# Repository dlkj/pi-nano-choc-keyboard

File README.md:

# pi-nano-choc-keyboard
Split ergo keyboard based on the Rasberry Pi Nano and Kailh Choc v1 switches

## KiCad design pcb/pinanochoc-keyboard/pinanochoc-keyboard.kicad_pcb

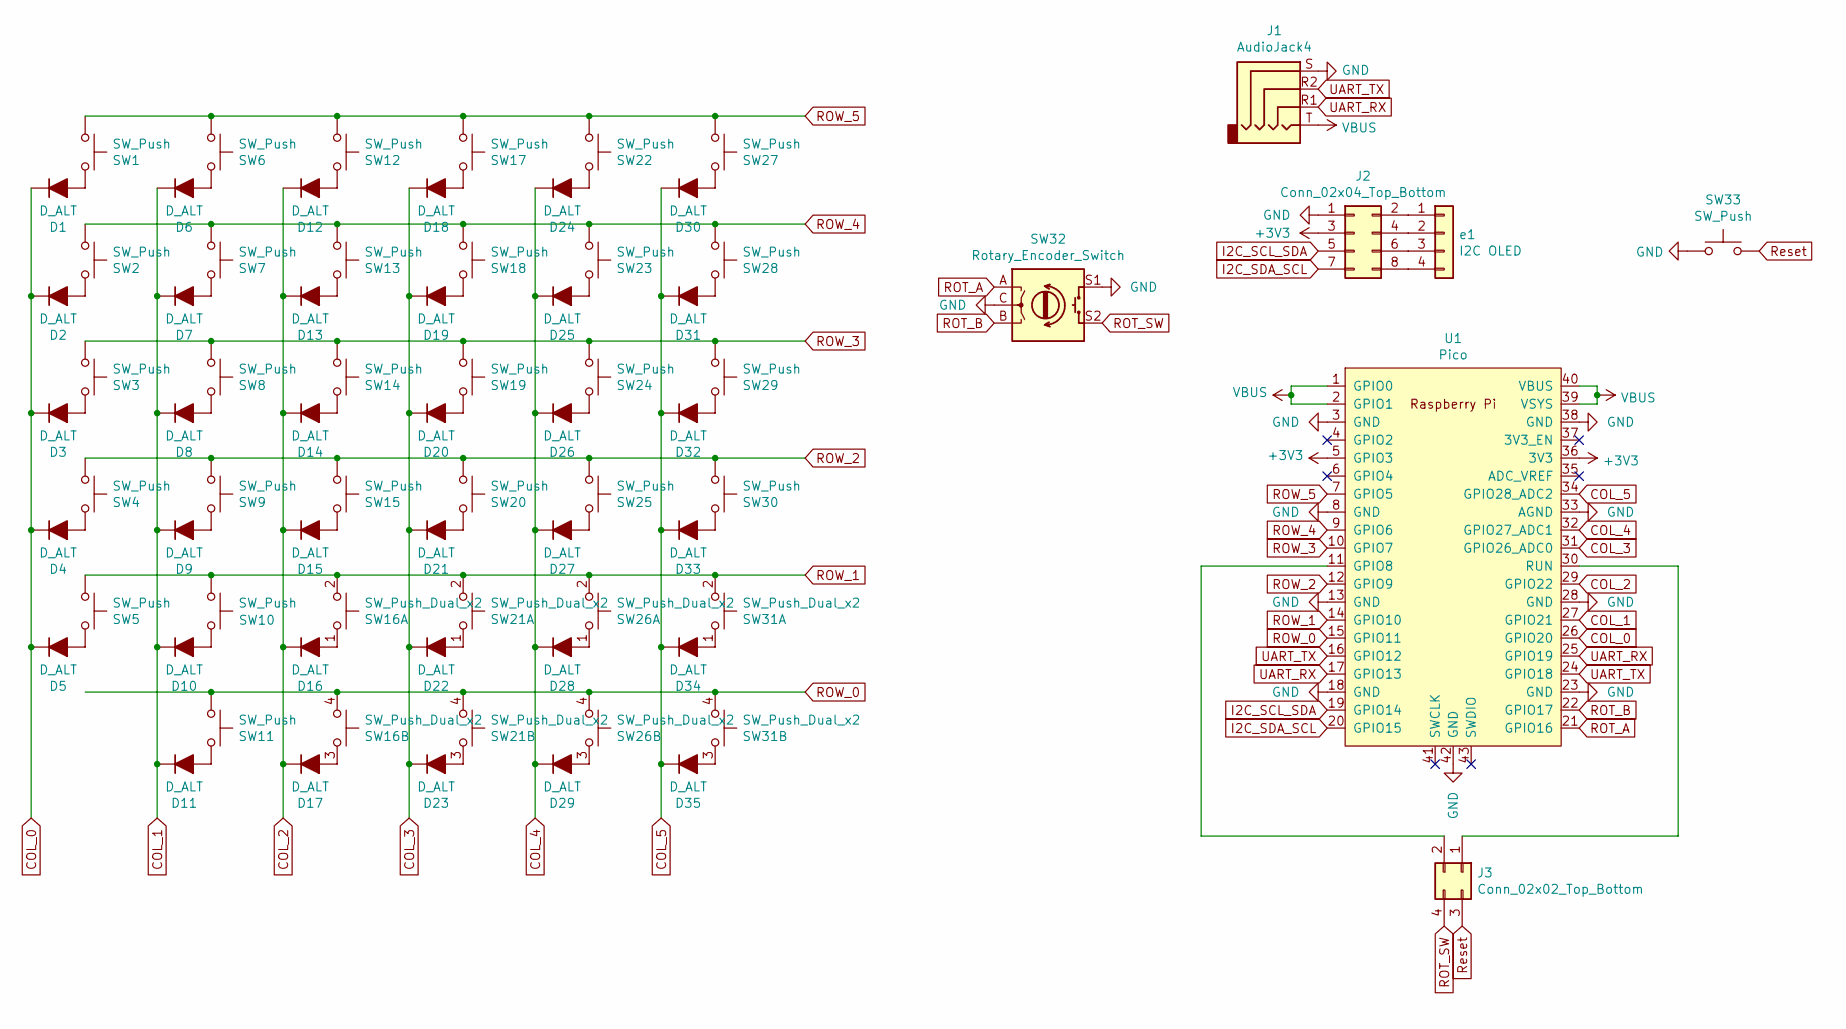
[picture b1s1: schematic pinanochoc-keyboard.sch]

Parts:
D1, D2, D3, D4, D5, D6, D7, D8, D9, D10, D11, D12, D13, D14, D15, D16, D17, D18, D19, D20, D21, D22, D23, D24, D25, D26, D27, D28, D29, D30, D31, D32, D33, D34, D35: D_ALT; D_DO-35_SOD27_P7.62mm_Horizontal
J1: AudioJack4; TRRS-PJ-320A_reversable
J2: Conn_02x04_Top_Bottom; PinHeader_2x04_P2.54mm_Vertical
J3: Conn_02x02_Top_Bottom; PinHeader_2x02_P2.54mm_Vertical
SW1, SW2, SW3, SW4, SW5, SW6, SW7, SW8, SW9, SW10, SW11, SW12, SW13, SW14, SW15, SW17, SW18, SW19, SW20, SW22, SW23, SW24, SW25, SW27, SW28, SW29, SW30: SW_Push; SW_PG1350_reversible
SW16, SW21, SW26, SW31: SW_Push_Dual_x2; SW_PG1350_reversible_double_rotatable
SW32: Rotary_Encoder_Switch; RotaryEncoder_Alps_EC11E-Switch_Vertical_H20mm
SW33: SW_Push; SW_PUSH_6mm
U1: Pico; RPi_Pico_SMD_TH_flipable
e1: I2C OLED; PinHeader_1x04_P2.54mm_Vertical

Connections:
+3V3: J2.3, U1.5 (GPIO3), U1.36 (3V3)
COL_0: D1.1 (K), D2.1 (K), D3.1 (K), D4.1 (K), D5.1 (K), U1.26 (GPIO20)
COL_1: D6.1 (K), D7.1 (K), D8.1 (K), D9.1 (K), D10.1 (K), D11.1 (K), U1.27 (GPIO21)
COL_2: D12.1 (K), D13.1 (K), D14.1 (K), D15.1 (K), D16.1 (K), D17.1 (K), U1.29 (GPIO22)
COL_3: D18.1 (K), D19.1 (K), D20.1 (K), D21.1 (K), D22.1 (K), D23.1 (K), U1.31 (GPIO26_ADC0)
COL_4: D24.1 (K), D25.1 (K), D26.1 (K), D27.1 (K), D28.1 (K), D29.1 (K), U1.32 (GPIO27_ADC1)
COL_5: D30.1 (K), D31.1 (K), D32.1 (K), D33.1 (K), D34.1 (K), D35.1 (K), U1.34 (GPIO28_ADC2)
GND: J1.S, J2.1, SW32.C, SW32.S1, SW33.1, U1.3 (GND), U1.8 (GND), U1.13 (GND), U1.18 (GND), U1.23 (GND), U1.28 (GND), U1.33 (AGND), U1.38 (GND), U1.42 (GND)
I2C_SCL_SDA: J2.5, U1.19 (GPIO14)
I2C_SDA_SCL: J2.7, U1.20 (GPIO15)
unnamed: D1.2 (A), SW1.1
unnamed: D2.2 (A), SW2.1
unnamed: D3.2 (A), SW3.1
unnamed: D4.2 (A), SW4.1
unnamed: D5.2 (A), SW5.1
unnamed: D6.2 (A), SW6.1
unnamed: D7.2 (A), SW7.1
unnamed: D8.2 (A), SW8.1
unnamed: D9.2 (A), SW9.1
unnamed: D10.2 (A), SW10.1
unnamed: D11.2 (A), SW11.1
unnamed: D12.2 (A), SW12.1
unnamed: D13.2 (A), SW13.1
unnamed: D14.2 (A), SW14.1
unnamed: D15.2 (A), SW15.1
unnamed: D16.2 (A), SW16.1 (C)
unnamed: D17.2 (A), SW16.3 (C)
unnamed: D18.2 (A), SW17.1
unnamed: D19.2 (A), SW18.1
unnamed: D20.2 (A), SW19.1
unnamed: D21.2 (A), SW20.1
unnamed: D22.2 (A), SW21.1 (C)
unnamed: D23.2 (A), SW21.3 (C)
unnamed: D24.2 (A), SW22.1
unnamed: D25.2 (A), SW23.1
unnamed: D26.2 (A), SW24.1
unnamed: D27.2 (A), SW25.1
unnamed: D28.2 (A), SW26.1 (C)
unnamed: D29.2 (A), SW26.3 (C)
unnamed: D30.2 (A), SW27.1
unnamed: D31.2 (A), SW28.1
unnamed: D32.2 (A), SW29.1
unnamed: D33.2 (A), SW30.1
unnamed: D34.2 (A), SW31.1 (C)
unnamed: D35.2 (A), SW31.3 (C)
unnamed: J2.2, e1.1
unnamed: J2.4, e1.2
unnamed: J2.6, e1.3
unnamed: J2.8, e1.4
unnamed: J3.1, U1.30 (RUN)
unnamed: J3.2, U1.11 (GPIO8)
ROT_A: SW32.A, U1.21 (GPIO16)
ROT_B: SW32.B, U1.22 (GPIO17)
ROT_SW: J3.4, SW32.S2
ROW_0: SW11.2, SW16.4 (D), SW21.4 (D), SW26.4 (D), SW31.4 (D), U1.15 (GPIO11)
ROW_1: SW5.2, SW10.2, SW16.2 (D), SW21.2 (D), SW26.2 (D), SW31.2 (D), U1.14 (GPIO10)
ROW_2: SW4.2, SW9.2, SW15.2, SW20.2, SW25.2, SW30.2, U1.12 (GPIO9)
ROW_3: SW3.2, SW8.2, SW14.2, SW19.2, SW24.2, SW29.2, U1.10 (GPIO7)
ROW_4: SW2.2, SW7.2, SW13.2, SW18.2, SW23.2, SW28.2, U1.9 (GPIO6)
ROW_5: SW1.2, SW6.2, SW12.2, SW17.2, SW22.2, SW27.2, U1.7 (GPIO5)
Reset: J3.3, SW33.2
UART_RX: J1.R1, U1.17 (GPIO13), U1.25 (GPIO19)
UART_TX: J1.R2, U1.16 (GPIO12), U1.24 (GPIO18)
VBUS: J1.T, U1.1 (GPIO0), U1.2 (GPIO1), U1.39 (VSYS), U1.40 (VBUS)

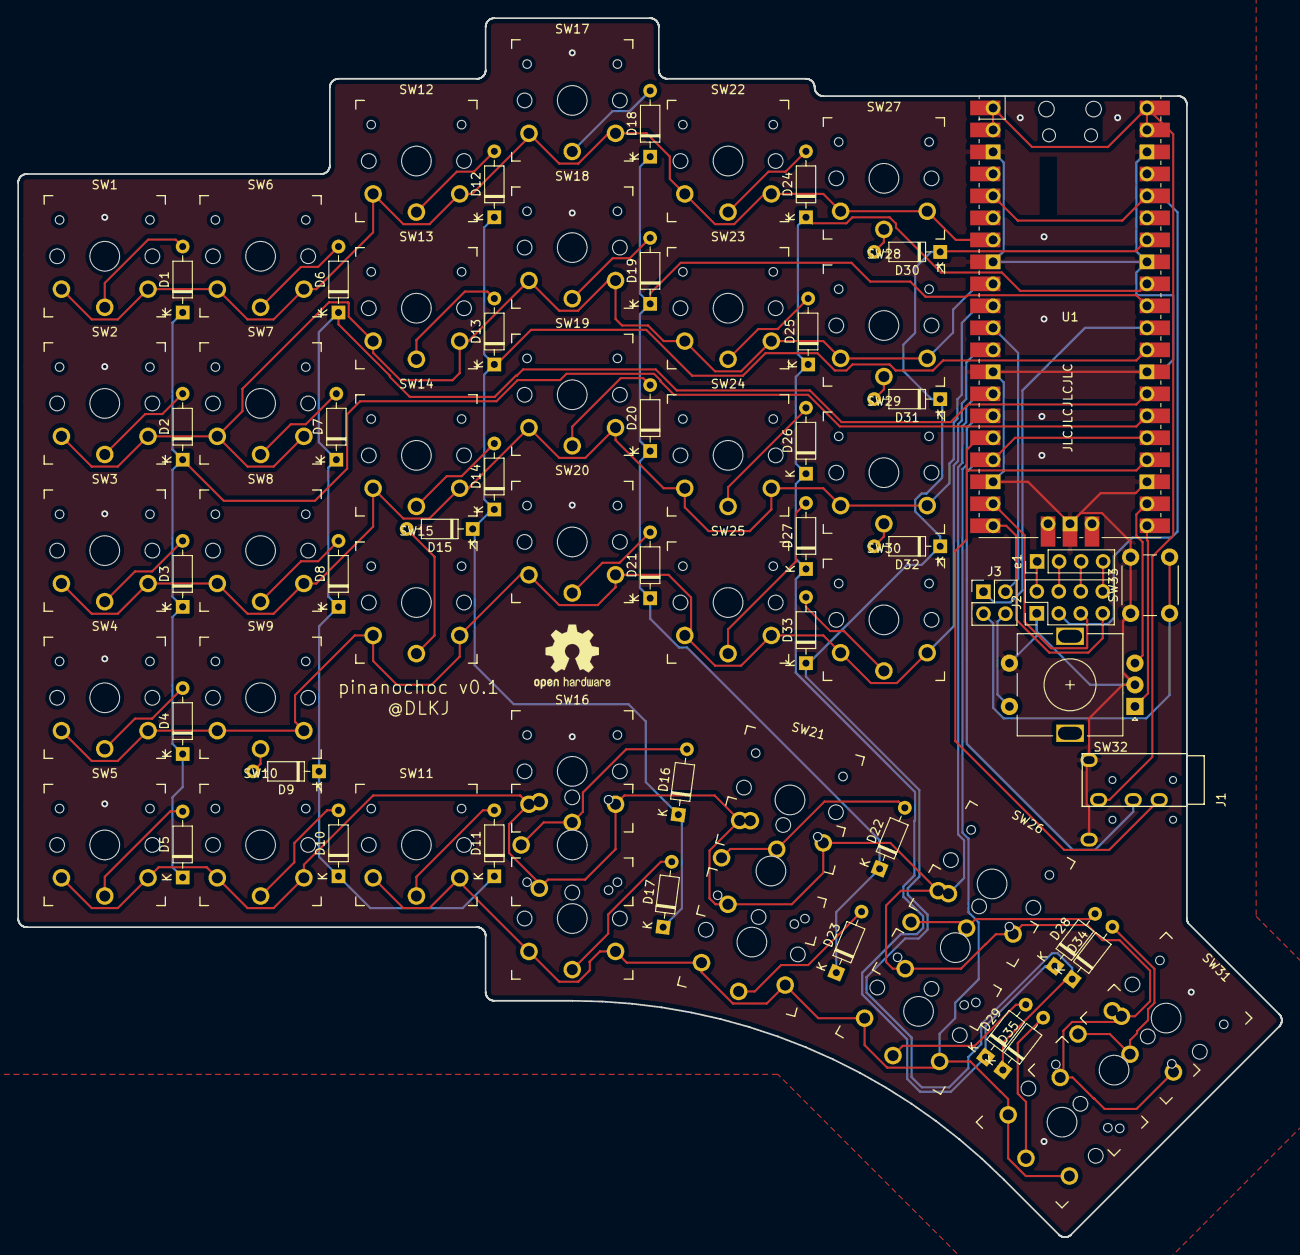
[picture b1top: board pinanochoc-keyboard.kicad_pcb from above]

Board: 2 copper layers, 146.0 x 140.8 mm, 73 parts (0 on the bottom side), 64 nets.

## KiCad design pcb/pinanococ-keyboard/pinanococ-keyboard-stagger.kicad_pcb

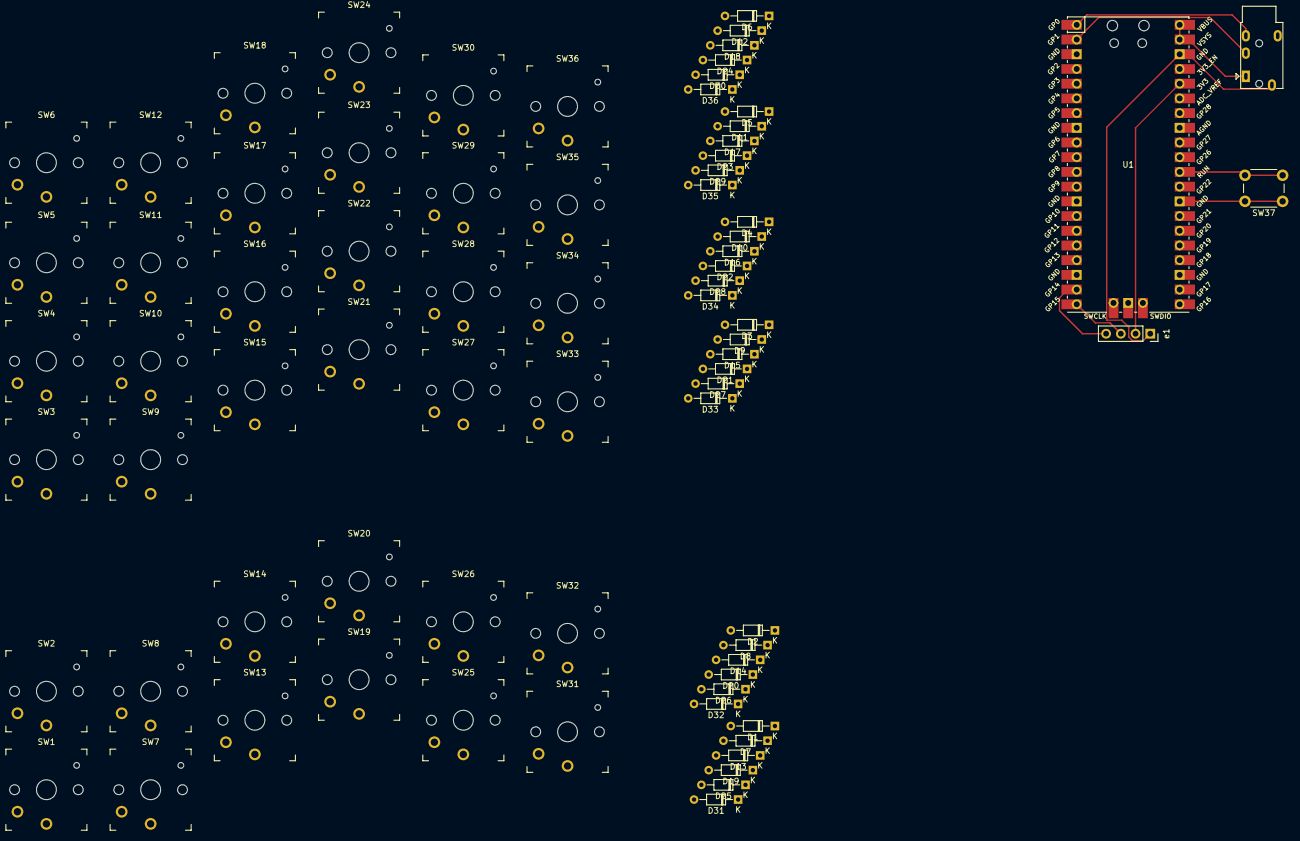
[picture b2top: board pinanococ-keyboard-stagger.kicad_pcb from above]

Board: 2 copper layers, 76 parts (0 on the bottom side), 57 nets.

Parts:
D1, D2, D3, D4, D5, D6, D7, D8, D9, D10, D11, D12, D13, D14, D15, D16, D17, D18, D19, D20, D21, D22, D23, D24, D25, D26, D27, D28, D29, D30, D31, D32, D33, D34, D35, D36: D_ALT; D_DO-34_SOD68_P7.62mm_Horizontal
J1: AudioJack4; Jack_3.5mm_PJ320E_Horizontal
SW1, SW2, SW3, SW4, SW5, SW6, SW7, SW8, SW9, SW10, SW11, SW12, SW13, SW14, SW15, SW16, SW17, SW18, SW19, SW20, SW21, SW22, SW23, SW24, SW25, SW26, SW27, SW28, SW29, SW30, SW31, SW32, SW33, SW34, SW35, SW36: SW_Push; SW_PG1350
SW37: SW_Push; SW_PUSH_6mm
U1: Pico; RPi_Pico_SMD_TH
e1: I2C OLED; PinSocket_1x04_P2.54mm_Vertical

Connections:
+3V3: U1.36, e1.2
COL_0: D1.1, D2.1, D3.1, D4.1, D5.1, D6.1, U1.11
COL_1: D7.1, D8.1, D9.1, D10.1, D11.1, D12.1, U1.12
COL_2: D13.1, D14.1, D15.1, D16.1, D17.1, D18.1, U1.14
COL_3: D19.1, D20.1, D21.1, D22.1, D23.1, D24.1, U1.15
COL_4: D25.1, D26.1, D27.1, D28.1, D29.1, D30.1, U1.16
COL_5: D31.1, D32.1, D33.1, D34.1, D35.1, D36.1, U1.17
GND: J1.S, U1.38, e1.1
GND1: SW37.1, U1.28
I2C_SCL: U1.20, e1.3
I2C_SDA: U1.19, e1.4
unnamed: D1.2, SW1.1
unnamed: D2.2, SW2.1
unnamed: D3.2, SW3.1
unnamed: D4.2, SW4.1
unnamed: D5.2, SW5.1
unnamed: D6.2, SW6.1
unnamed: D7.2, SW7.1
unnamed: D8.2, SW8.1
unnamed: D9.2, SW9.1
unnamed: D10.2, SW10.1
unnamed: D11.2, SW11.1
unnamed: D12.2, SW12.1
unnamed: D13.2, SW13.1
unnamed: D14.2, SW14.1
unnamed: D15.2, SW15.1
unnamed: D16.2, SW16.1
unnamed: D17.2, SW17.1
unnamed: D18.2, SW18.1
unnamed: D19.2, SW19.1
unnamed: D20.2, SW20.1
unnamed: D21.2, SW21.1
unnamed: D22.2, SW22.1
unnamed: D23.2, SW23.1
unnamed: D24.2, SW24.1
unnamed: D25.2, SW25.1
unnamed: D26.2, SW26.1
unnamed: D27.2, SW27.1
unnamed: D28.2, SW28.1
unnamed: D29.2, SW29.1
unnamed: D30.2, SW30.1
unnamed: D31.2, SW31.1
unnamed: D32.2, SW32.1
unnamed: D33.2, SW33.1
unnamed: D34.2, SW34.1
unnamed: D35.2, SW35.1
unnamed: D36.2, SW36.1
ROW_0: SW1.2, SW7.2, SW13.2, SW19.2, SW25.2, SW31.2, U1.4
ROW_1: SW2.2, SW8.2, SW14.2, SW20.2, SW26.2, SW32.2, U1.5
ROW_2: SW3.2, SW9.2, SW15.2, SW21.2, SW27.2, SW33.2, U1.6
ROW_3: SW4.2, SW10.2, SW16.2, SW22.2, SW28.2, SW34.2, U1.7
ROW_4: SW5.2, SW11.2, SW17.2, SW23.2, SW29.2, SW35.2, U1.9
ROW_5: SW6.2, SW12.2, SW18.2, SW24.2, SW30.2, SW36.2, U1.10
Reset: SW37.2, U1.30
UART_RX: J1.R1, U1.2
UART_TX: J1.R2, U1.1
VBUS: J1.T, U1.39, U1.40

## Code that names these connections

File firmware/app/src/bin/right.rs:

#![no_std]
#![no_main]

use core::cell::RefCell;
use core::cmp::Ordering;
use core::convert::Infallible;

use cortex_m::interrupt::Mutex;
use cortex_m::peripheral::syst::SystClkSource;
use cortex_m_rt::entry;
use cortex_m_rt::exception;
use embedded_hal::digital::v2::InputPin;
use embedded_hal::digital::v2::OutputPin;
use embedded_hal::digital::v2::ToggleableOutputPin;
use embedded_hal::prelude::_embedded_hal_serial_Write;
use embedded_time::duration::Milliseconds;
use embedded_time::Clock;
use log::{info, LevelFilter};
use nb::block;
use panic_persist as _;
use rp_pico::hal::clocks::{self, ClocksManager};
use rp_pico::hal::gpio::PullUpInput;
use rp_pico::hal::gpio::{FunctionUart, Pin};
use rp_pico::hal::uart::{self, UartPeripheral};
use rp_pico::hal::{self, Clock as _};
use rp_pico::{
    hal::{
        gpio::DynPin,
        pac::{self},
        sio::Sio,
        watchdog::Watchdog,
    },
    Pins,
};
use ssd1306::{prelude::*, size::DisplaySize128x32, I2CDisplayInterface, Ssd1306};

use app::keyboard::*;
use app::rotary_enc::RotaryEncoder;
use app::SyncTimerClock;

type TimerShared = (
    DiodePinMatrix<DynPin, DynPin>,
    RotaryEncoder<
        Pin<hal::gpio::pin::bank0::Gpio14, PullUpInput>,
        Pin<hal::gpio::pin::bank0::Gpio15, PullUpInput>,
        Infallible,
    >,
);

static TIMER_SHARED: Mutex<RefCell<Option<TimerShared>>> = Mutex::new(RefCell::new(None));

const INPUT_SAMPLE: Milliseconds = Milliseconds(10);
const DISPLAY_UPDATE: Milliseconds = Milliseconds(20);

#[entry]
fn main() -> ! {
    let mut pac = pac::Peripherals::take().unwrap();
    let mut core = pac::CorePeripherals::take().unwrap();

    let mut watchdog = Watchdog::new(pac.WATCHDOG);

    let clocks: ClocksManager = clocks::init_clocks_and_plls(
        rp_pico::XOSC_CRYSTAL_FREQ,
        pac.XOSC,
        pac.CLOCKS,
        pac.PLL_SYS,
        pac.PLL_USB,
        &mut pac.RESETS,
        &mut watchdog,
    )
    .ok()
    .unwrap();

    let sio = Sio::new(pac.SIO);
    let pins = Pins::new(
        pac.IO_BANK0,
        pac.PADS_BANK0,
        sio.gpio_bank0,
        &mut pac.RESETS,
    );

    static mut CLOCK: Option<SyncTimerClock> = None;
    let clock = unsafe {
        CLOCK = Some(SyncTimerClock::new(hal::Timer::new(
            pac.TIMER,
            &mut pac.RESETS,
        )));
        CLOCK.as_ref().unwrap()
    };

    //Init display
    let scl_pin = pins.gpio17.into_mode::<rp_pico::hal::gpio::FunctionI2C>();
    let sda_pin = pins.gpio16.into_mode::<rp_pico::hal::gpio::FunctionI2C>();

    let i2c = rp_pico::hal::i2c::I2C::new_controller(
        pac.I2C0,
        sda_pin,
        scl_pin,
        embedded_time::rate::Extensions::kHz(400),
        &mut pac.RESETS,
        clocks.peripheral_clock.freq(),
    );

    let interface = I2CDisplayInterface::new(i2c);
    let mut display = Ssd1306::new(interface, DisplaySize128x32, DisplayRotation::Rotate90)
        .into_buffered_graphics_mode();
    display.init().unwrap();
    display.flush().unwrap();
    let mut oled_display = app::oled_display::OledDisplay::new(display, clock);

    app::check_for_persisted_panic(&mut oled_display);

    log::set_max_level(LevelFilter::Info);

    // Enable the USB interrupt
    unsafe {
        pac::NVIC::unmask(hal::pac::Interrupt::USBCTRL_IRQ);
    };

    let cols: [DynPin; 6] = [
        pins.gpio5.into_pull_down_input().into(),
        pins.gpio6.into_pull_down_input().into(),
        pins.gpio7.into_pull_down_input().into(),
        pins.gpio9.into_pull_down_input().into(),
        pins.gpio10.into_pull_down_input().into(),
        pins.gpio11.into_pull_down_input().into(),
    ];

    let mut rows: [DynPin; 6] = [
        pins.gpio28.into_push_pull_output().into(),
        pins.gpio27.into_push_pull_output().into(),
        pins.gpio26.into_push_pull_output().into(),
        pins.gpio22.into_push_pull_output().into(),
        pins.gpio21.into_push_pull_output().into(),
        pins.gpio20.into_push_pull_output().into(),
    ];

    for p in &mut rows {
        p.set_low().unwrap();
    }

    let rot_button = pins.gpio8.into_pull_up_input();

    let rot_b = pins.gpio15.into_pull_up_input();
    let rot_a = pins.gpio14.into_pull_up_input();

    let rot_enc = RotaryEncoder::new(rot_a, rot_b);

    let tx_pin = pins.gpio12.into_mode::<FunctionUart>();
    let rx_pin = pins.gpio13.into_mode::<FunctionUart>();

    let mut uart = UartPeripheral::<_, _, _>::new(pac.UART0, (tx_pin, rx_pin), &mut pac.RESETS)
        .enable(
            uart::common_configs::_19200_8_N_1,
            clocks.peripheral_clock.freq(),
        )
        .unwrap();

    // Splash screen
    oled_display.draw_text_screen("Starting...").unwrap();

    info!("Starting");

    //1ms timer
    let reload_value = 1000 - 1;
    core.SYST.set_reload(reload_value);
    core.SYST.clear_current();
    //External clock, driven by the Watchdog - 1 tick per us
    core.SYST.set_clock_source(SystClkSource::External);
    core.SYST.enable_interrupt();
    core.SYST.enable_counter();

    let matrix = DiodePinMatrix::new(rows, cols);

    cortex_m::interrupt::free(|cs| {
        TIMER_SHARED.borrow(cs).replace(Some((matrix, rot_enc)));
    });

    let mut input_timer = clock
        .new_timer(INPUT_SAMPLE)
        .into_periodic()
        .start()
        .unwrap();

    let mut display_timer = clock
        .new_timer(DISPLAY_UPDATE)
        .into_periodic()
        .start()
        .unwrap();

    let mut led = pins.led.into_push_pull_output();

    info!("Running main loop");
    loop {
        //10ms
        if input_timer.period_complete().unwrap() {
            //100Hz or slower
            let (keys, rot) = cortex_m::interrupt::free(|cs| {
                let mut timer_ref = TIMER_SHARED.borrow(cs).borrow_mut();

                let (ref mut matrix, ref mut rot_enc) = timer_ref.as_mut().unwrap();
                (
                    matrix.keys().expect("Failed to get matrix keys"),
                    rot_enc.rel_value(),
                )
            });

            let mut pressed_keys: arrayvec::ArrayVec<usize, 64> = keys
                .iter()
                .enumerate()
                .filter_map(|(i, &k)| k.pressed.then(|| i))
                .collect();

            if rot_button.is_low().unwrap() {
                pressed_keys.push(36);
            }
            match rot.cmp(&0) {
                Ordering::Less => pressed_keys.push(37),
                Ordering::Equal => {}
                Ordering::Greater => {
                    pressed_keys.push(38);
                }
            }

            led.toggle().unwrap();
            for &k in &pressed_keys {
                block!(uart.write(k as u8)).unwrap();
            }
            block!(uart.write(0xFF)).unwrap();
            led.toggle().unwrap();

            if display_timer.period_complete().unwrap() {
                oled_display.draw_right_display(&pressed_keys[..]).ok();
            }
        }
    }
}

#[exception]
fn SysTick() {
    cortex_m::interrupt::free(|cs| {
        let mut timer_ref = TIMER_SHARED.borrow(cs).borrow_mut();
        if timer_ref.is_none() {
            return;
        }

        let (ref mut matrix, ref mut rot_enc) = timer_ref.as_mut().unwrap();
        rot_enc.update();
        matrix.update().expect("Failed to update keys");
    });

    cortex_m::asm::sev();
}

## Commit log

2021-12-21 WIP left hand pcb
2021-12-22 first version of keyboard physical layout in cad
2021-12-22 pcb component layout
2021-12-22 inital pcb layout with tracks
2021-12-23 add pcb layout and edge renders
2021-12-23 reannotated flippable schematic
2021-12-23 first draft flipable footprints with scematic
2021-12-23 inital switch pcb layout
2021-12-23 first pass tracks for pcb
2021-12-23 v0.1 pcb layout
2021-12-23 gerbers for v0.1
2021-12-23 rename pinanococ to pinanochoc and fix typo on silk
2021-12-29 inital firmware
2021-12-30 implemented matrix scanning
2021-12-30 oled display support
2021-12-31 rename app to left
2021-12-31 create binary for right hand
2022-01-01 restructure both binaries to reference a single lib of code
2022-01-01 first working basic layout
2022-01-02 factor shared runtime out of each keyboard binary
2022-01-02 very basic UART functionality
2022-01-03 keymap diagram
2022-01-03 basic layer support
2022-01-03 change right hand to serial link
2022-01-04 enable dependabot
2022-01-04 add 2nd space key
2022-01-04 fix slice size panic
2022-01-04 add keyboard leds to screen
2022-01-04 remove uart example code comment
2022-01-04 implemented clippy sugestions
2022-01-04 new prettier display for left
2022-01-04 added screen saver
2022-01-05 display controller to include screensaver logic
2022-01-05 starfield screensaver
2022-01-13 moved to usbd-hid-devices
2022-01-13 remove serial logging - cause endless loop of logging over usb
2022-01-13 swap upper and lower keymaps
2022-01-13 added missing usb interupt handler
2022-01-13 remove serial, increase screen saver timeout
2022-01-13 switch away from interupts while it breaks boot suport
2022-01-13 fix leds and uart init panic
2022-01-14 More all mut usb calls into the poll block
2022-01-14 Sceensaver now stops on any display change, show usb status
2022-01-14 It was the display breaking windows all along
2022-01-15 Move all the usb stuff back to interupts, move keymap to own file
2022-01-15 Add ram dump panic handler and lots of cleanup
2022-01-15 Sync incoming serial data before reading keycodes
2022-01-15 Fix broken key reporting and usb status
2022-01-16 Fix and refine panic persist and usb boot on panic
2022-02-25 exclude ide files
2022-02-26 updated to latest usb-hid-devices lib
2022-02-26 Added basic rot encoder support to left
2022-02-27 Disable layer 2, move left display into a time loop
2022-03-03 moved left input sampling on to timer irq
2022-03-06 changed clock to u64 to avoid wrapping issue
2022-03-14 Update rp-pico requirement from 0.2 to 0.3 in /firmware
    Updates the requirements on [rp-pico](https://github.com/rp-rs/rp-hal) to permit the latest version.
    - [Release notes](https://github.com/rp-rs/rp-hal/releases)
    - [Commits](https://github.com/rp-rs/rp-hal/compare/rp-pico-0.2.0...rp-pico-v0.3.0)
    ---
    updated-dependencies:
    - dependency-name: rp-pico
2022-04-02 Upgrade to usbd-human-interface-device
2022-04-06 basic right rotary encoder support
2022-05-14 relax dependency versions
2022-05-16 Update usbd-human-interface-device requirement in /firmware
    Updates the requirements on [usbd-human-interface-device](https://github.com/dlkj/usbd-human-interface-device) to permit the latest version.
    - [Release notes](https://github.com/dlkj/usbd-human-interface-device/releases)
    - [Commits](https://github.com/dlkj/usbd-human-interface-device/compare/v0.1.1...v0.2.0)
    ---
    updated-dependencies:
    - dependency-name: usbd-human-interface-device
2022-05-21 Increase debouncing, fix display update timing, dim screen for screensaver
2022-06-14 Update rp-pico requirement from 0.3 to 0.4 in /firmware
    Updates the requirements on [rp-pico](https://github.com/rp-rs/rp-hal) to permit the latest version.
    - [Release notes](https://github.com/rp-rs/rp-hal/releases)
    - [Commits](https://github.com/rp-rs/rp-hal/compare/rp-pico-v0.3.0...v0.4.0)
    ---
    updated-dependencies:
    - dependency-name: rp-pico
2022-08-26 Update rp-pico requirement from 0.4 to 0.5 in /firmware
    Updates the requirements on [rp-pico](https://github.com/rp-rs/rp-hal) to permit the latest version.
    - [Release notes](https://github.com/rp-rs/rp-hal/releases)
    - [Commits](https://github.com/rp-rs/rp-hal/compare/v0.4.0...v0.5.0)
    ---
    updated-dependencies:
    - dependency-name: rp-pico
2022-09-12 Update usbd-human-interface-device requirement in /firmware
    Updates the requirements on [usbd-human-interface-device](https://github.com/dlkj/usbd-human-interface-device) to permit the latest version.
    - [Release notes](https://github.com/dlkj/usbd-human-interface-device/releases)
    - [Commits](https://github.com/dlkj/usbd-human-interface-device/compare/v0.2.0...v0.3.1)
    ---
    updated-dependencies:
    - dependency-name: usbd-human-interface-device
2022-12-12 Update rp-pico requirement from 0.4 to 0.6 in /firmware
    Updates the requirements on [rp-pico](https://github.com/rp-rs/rp-hal-boards) to permit the latest version.
    - [Release notes](https://github.com/rp-rs/rp-hal-boards/releases)
    - [Commits](https://github.com/rp-rs/rp-hal-boards/compare/arduino_nano_connect-0.4.0...rp-pico-0.6.0)
    ---
    updated-dependencies:
    - dependency-name: rp-pico
2023-02-21 Update rp-pico requirement from 0.4 to 0.7 in /firmware
    Updates the requirements on [rp-pico](https://github.com/rp-rs/rp-hal-boards) to permit the latest version.
    - [Release notes](https://github.com/rp-rs/rp-hal-boards/releases)
    - [Commits](https://github.com/rp-rs/rp-hal-boards/commits)
    ---
    updated-dependencies:
    - dependency-name: rp-pico
